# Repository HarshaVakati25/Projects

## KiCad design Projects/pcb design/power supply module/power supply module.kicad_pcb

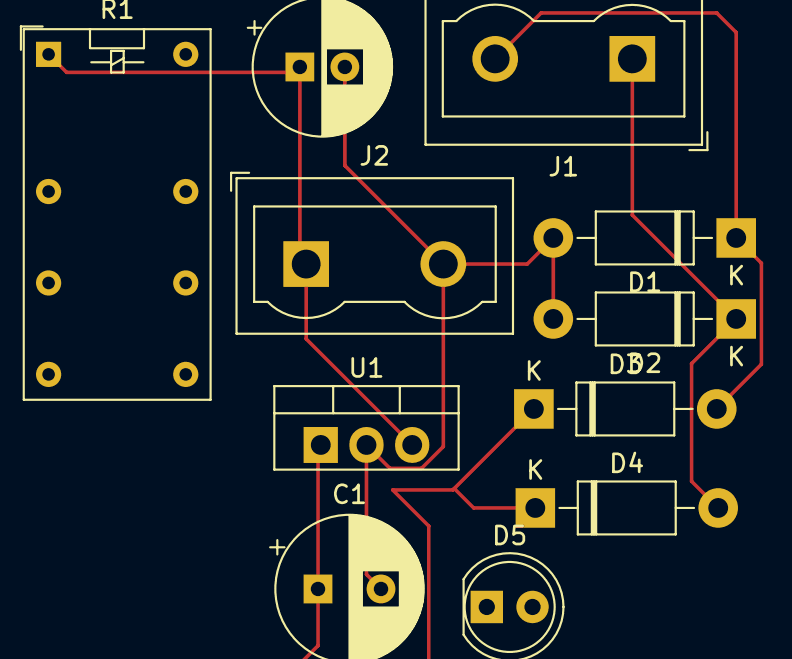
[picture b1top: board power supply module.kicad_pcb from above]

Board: 2 copper layers, 11 parts (0 on the bottom side), 5 nets.

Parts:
C1: 470 uf 25v; CP_Radial_D8.0mm_P3.50mm
C2: 100 uf; CP_Radial_D7.5mm_P2.50mm
D1, D2, D3, D4: 1N4007; D_DO-41_SOD81_P10.16mm_Horizontal
D5: LED; LED_D5.0mm
J1, J2: Screw_Terminal_01x02; TerminalBlock_Wuerth_691311400102_P7.62mm
R1: 1k; Relay_DPDT_Omron_G5V-2
U1: LM7805_TO220; TO-220-3_Vertical

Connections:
unnamed: C1.2, C2.2, D1.2 (A), D2.2 (A), D5.1 (K), J2.2, U1.2 (GND)
unnamed: D1.1 (K), D3.2 (A), J1.2
unnamed: D2.1 (K), D4.2 (A), J1.1
unnamed: C1.1, D3.1 (K), D4.1 (K), U1.1 (VI)
unnamed: C2.1, J2.1, R1.1, U1.3 (VO)
